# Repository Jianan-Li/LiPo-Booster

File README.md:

LiPo-Booster
============
A breadboard-friendly boost converter board based on TPS61230 from Texus Instrument. The input voltage from a single cell LiPo battery is converted to 5V for use with 5V systems.

v1: Minimum component count

v2: Configurable UVLO using three additional resistors

Please refer to the TPS61230 datasheet for UVLO resistors calculation.

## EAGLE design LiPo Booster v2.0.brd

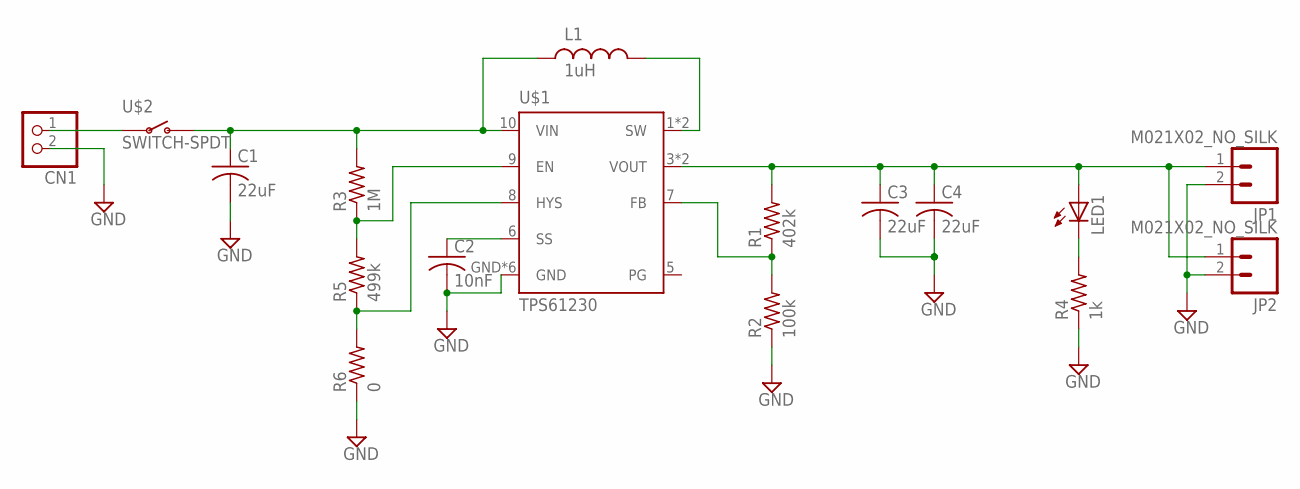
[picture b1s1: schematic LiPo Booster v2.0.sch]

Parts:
C1, C3, C4: 22uF; C0603K
C2: 10nF; C0603K
CN1: JST_2PIN-SMT-RA; JST-PH-2-SMT-RA
JP1, JP2: M021X02_NO_SILK; 1X02_NO_SILK
L1: 1uH; XFL4020
LED1: LEDCHIPLED_0603; CHIPLED_0603
R1: 402k; R0603
R2: 100k; R0603
R3: 1M; R0603
R4: 1k; R0603
R5: 499k; R0603
R6: 0; R0603
U$1: TPS61230; DRC-S-PVSON-N11
U$2: SWITCH-SPDT; JS102011

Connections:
GND: C1.2, C2.2, C3.2, C4.2, CN1.2 (1), JP1.2, JP2.2, R2.1, R4.1, R6.1, U$1.GND, U$1.GND@1 (GND), U$1.GND@2 (GND), U$1.GND@3 (GND), U$1.GND@4 (GND), U$1.GND@5 (GND)
IND: L1.P$2 (2), U$1.1 (SW), U$1.2 (SW)
unnamed: R3.1, R5.2, U$1.9 (EN)
unnamed: LED1.C, R4.2
unnamed: C2.1, U$1.6 (SS)
unnamed: R5.1, R6.2, U$1.8 (HYS)
unnamed: R1.1, R2.2, U$1.7 (FB)
PG: U$1.5 (PG)
VBATT: CN1.1 (2), U$2.P$3
VIN: C1.1, L1.P$1 (1), R3.2, U$1.10 (VIN), U$2.P$2 (O)
VOUT: C3.1, C4.1, JP1.1, JP2.1, LED1.A, R1.2, U$1.3 (VOUT), U$1.4 (VOUT)

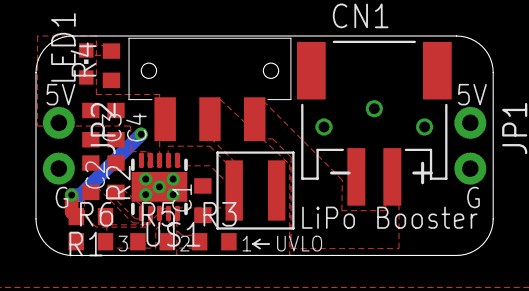
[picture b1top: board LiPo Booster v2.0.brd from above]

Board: 2 copper layers, 25.4 x 12.2 mm, 18 parts (0 on the bottom side), 10 nets.

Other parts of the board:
U$3: ARROW<--

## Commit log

2014-05-15 Lipo Booster v1
    Lipo Booster v1 based on TPS61230
2014-05-15 Rename Lipo Booster v1.brd to LiPo Booster v1.brd
2014-05-15 Rename Lipo Booster v1.sch to LiPo Booster v1.sch
2014-05-15 v1.1
2014-05-15 OSH Park Rendering
2014-05-16 BOM v1.1
2014-05-18 Minor adjustments of component placement
2014-05-18 v2 with configurable UVLO
2014-05-29 v1.2
2014-05-29 v2.0

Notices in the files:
parts and their libraries:
SparkFun-Connectors: Licensing: Creative Commons ShareAlike 4.0 International - https://creativecommons.org/licenses/by-sa/4.0
